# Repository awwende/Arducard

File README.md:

Arducard
========

The arduino business card game

The Arducard is released under the Creative Commons License, feel free to use as is or make any changes you wish.
The only thing that is asked is that any changes made remain open source.

Changes that need to be made:

-On the board file, example text is provided, but should be replaced with your name and contact information (or just deleted)

-The intro screen found at line 94 of the firmware should be replaced with your own unique message

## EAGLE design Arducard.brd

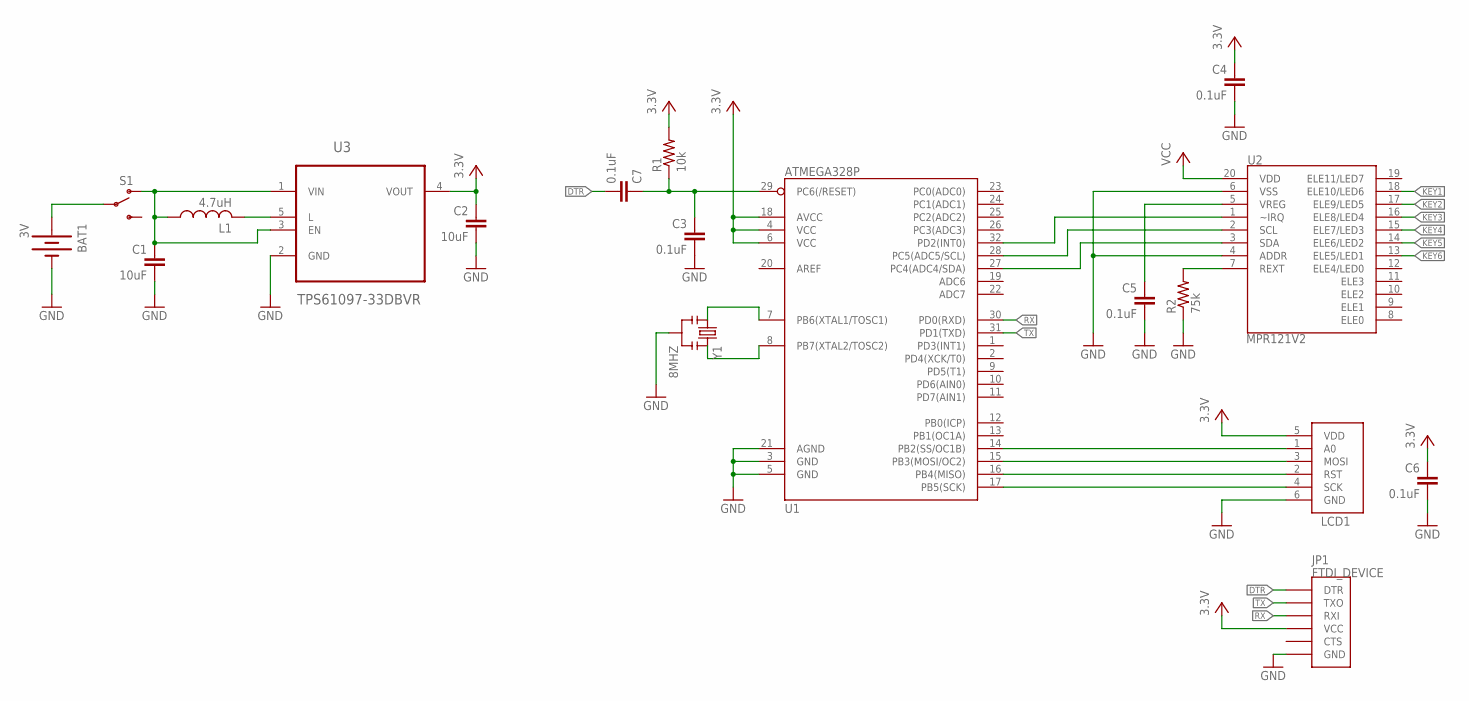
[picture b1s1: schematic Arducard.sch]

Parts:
BAT1: 3V; BATTCON_20MM_4LEGS
C1, C2: 10uF; C0603K
C3, C4, C5, C6, C7: 0.1uF; C0603K
JP1: FTDI_DEVICE; FTDI_DEVICE_SIDE
L1: 4.7uH; L2012C; MPN CKS21254R7M-T
LCD1: LCD
R1: 10k; R0603
R2: 75k; R0603
S1: SWITCH-SPDTSMD2; SWITCH-SPDT-SMD
U1: ATMEGA328P; TQFP32-08
U2: MPR121V2; QFN-20-0.4MM-V2
U3: TPS61097-33DBVR; SOT95P280X145-5N
Y1: 8MHZ; RESONATOR-SMD

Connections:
DTR: C7.2, JP1.P$1 (DTR)
GND: BAT1.2 (-), C1.2, C2.2, C3.2, C4.2, C5.2, C6.2, JP1.P$6 (GND), LCD1.6 (GND), R2.1, U1.3 (GND), U1.5 (GND), U1.21 (AGND), U2.4 (ADDR), U2.6 (VSS), U3.2 (GND), Y1.2
KEY1: U2.18 (ELE10/LED6)
KEY2: U2.17 (ELE9/LED5)
KEY3: U2.16 (ELE8/LED4)
KEY4: U2.15 (ELE7/LED3)
KEY5: U2.14 (ELE6/LED2)
KEY6: U2.13 (ELE5/LED1)
unnamed: LCD1.4 (SCK), U1.17 (PB5(SCK))
unnamed: LCD1.2 (RST), U1.16 (PB4(MISO))
unnamed: LCD1.3 (MOSI), U1.15 (PB3(MOSI/OC2))
unnamed: LCD1.1 (A0), U1.14 (PB2(SS/OC1B))
unnamed: R2.2, U2.7 (REXT)
unnamed: C5.1, U2.5 (VREG)
unnamed: U1.32 (PD2(INT0)), U2.1 (~IRQ)
unnamed: U1.28 (PC5(ADC5/SCL)), U2.2 (SCL)
unnamed: U1.27 (PC4(ADC4/SDA)), U2.3 (SDA)
unnamed: U1.7 (PB6(XTAL1/TOSC1)), Y1.1
unnamed: U1.8 (PB7(XTAL2/TOSC2)), Y1.3
unnamed: C3.1, C7.1, R1.1, U1.29 (PC6(/RESET))
unnamed: L1.2, U3.5 (L)
unnamed: C1.1, L1.1, S1.1 (O), U3.1 (VIN), U3.3 (EN)
unnamed: BAT1.P$2 (+), S1.2
RX: JP1.P$3 (RXI), U1.30 (PD0(RXD))
TX: JP1.P$2 (TXO), U1.31 (PD1(TXD))
VCC: C2.1, C4.1, C6.1, JP1.P$4 (VCC), LCD1.5 (VDD), R1.2, U1.4 (VCC), U1.6 (VCC), U1.18 (AVCC), U2.20 (VDD), U3.4 (VOUT)

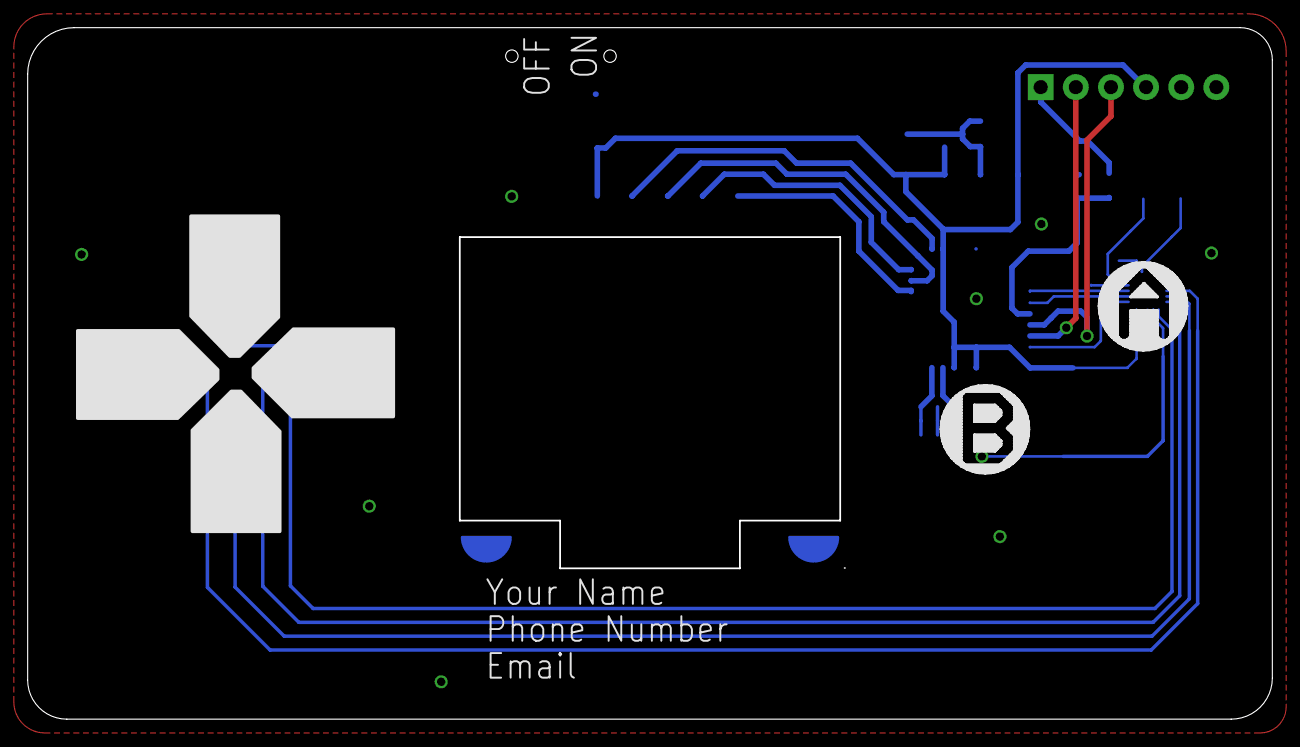
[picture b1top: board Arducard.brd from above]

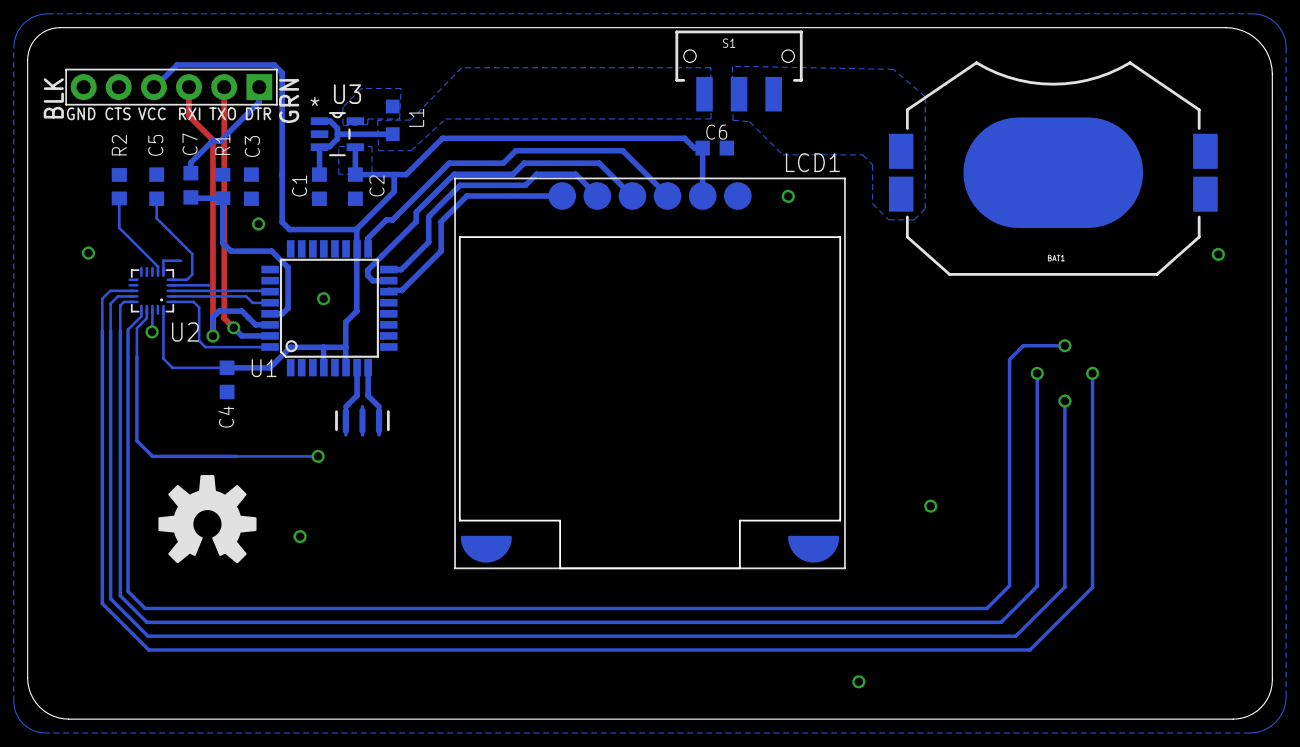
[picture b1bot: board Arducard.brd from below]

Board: 2 copper layers, 89.9 x 49.9 mm, 19 parts (19 on the bottom side), 20 nets.

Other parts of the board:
U$1: OSHW-LOGO-L

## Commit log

2014-08-21 :boom::camel: Added .gitattributes & .gitignore files
2014-08-21 Revert ":boom::camel: Added .gitattributes & .gitignore files"
    This reverts commit a5d2def3bced22702fbcb82b638593eda79e8fb8.
2014-08-21 Added Eagle files and Arduino Code
2014-08-21 Revert "Added Eagle files and Arduino Code"
    This reverts commit 2e4201ac74604f6116833c5673f0b3d6424c5c66.
2014-08-21 Eagle Files for the Arducard
2014-08-21 Arduino Code
2014-08-21 Removed
2014-08-21 Eagle Board File
2014-08-21 Eagle Schematic File
2014-08-21 Bill of Materials
2014-09-04 Fixed minor errors
2014-09-04 Arducard Schematic (Eagle)
2014-09-04 Arducard Board (Eagle)
2014-09-04 PDF Schematic
2014-09-04 Board File
2014-09-04 Schematic
2014-09-04 Schematic File
2014-09-05 Deleted
2014-09-05 Board
2014-09-07 Eagle PCB
2014-09-07 Eagle Schematic

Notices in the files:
parts and their libraries:
SparkFun-DigitalIC: Licensing: Creative Commons ShareAlike 4.0 International - https://creativecommons.org/licenses/by-sa/4.0
